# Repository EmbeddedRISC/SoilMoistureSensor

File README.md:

# SoilMoistureSensor
Contains data for Arduino Based Soil Moisture Sensors

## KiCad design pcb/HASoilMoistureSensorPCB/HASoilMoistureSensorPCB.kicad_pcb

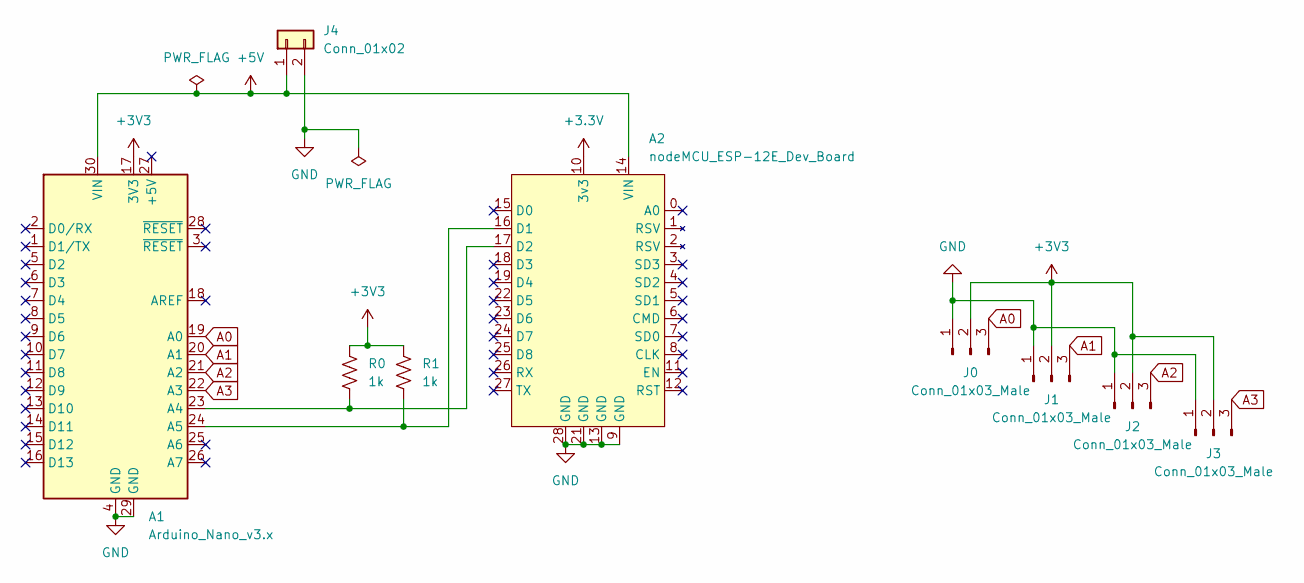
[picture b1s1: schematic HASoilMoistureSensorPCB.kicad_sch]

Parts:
A1: Arduino_Nano_v3.x; Arduino_Nano
A2: nodeMCU_ESP-12E_Dev_Board; nodeMCU_ESP-12e_Through-Hole
J0, J1, J2, J3: Conn_01x03_Male; JST_PH_B3B-PH-K_1x03_P2.00mm_Vertical
J4: Conn_01x02; JST_PH_B2B-PH-K_1x02_P2.00mm_Vertical
R0, R1: 1k; R_Axial_DIN0207_L6.3mm_D2.5mm_P2.54mm_Vertical

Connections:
+3.3V: A2.10 (3v3), A2.20 (3v3), A2.29 (3v3)
+3V3: A1.17 (3V3), J0.2, J1.2, J2.2, J3.2, R0.1, R1.1
+5V: A1.30 (VIN), A2.14 (VIN), J4.1
A0: A1.19 (A0), J0.3
A1: A1.20 (A1), J1.3
A2: A1.21 (A2), J2.3
A3: A1.22 (A3), J3.3
GND: A1.4 (GND), A1.29 (GND), A2.9 (GND), A2.13 (GND), A2.21 (GND), A2.28 (GND), J0.1, J1.1, J2.1, J3.1, J4.2
unnamed: A1.23 (A4), A2.17 (D2), R0.2
unnamed: A1.24 (A5), A2.16 (D1), R1.2

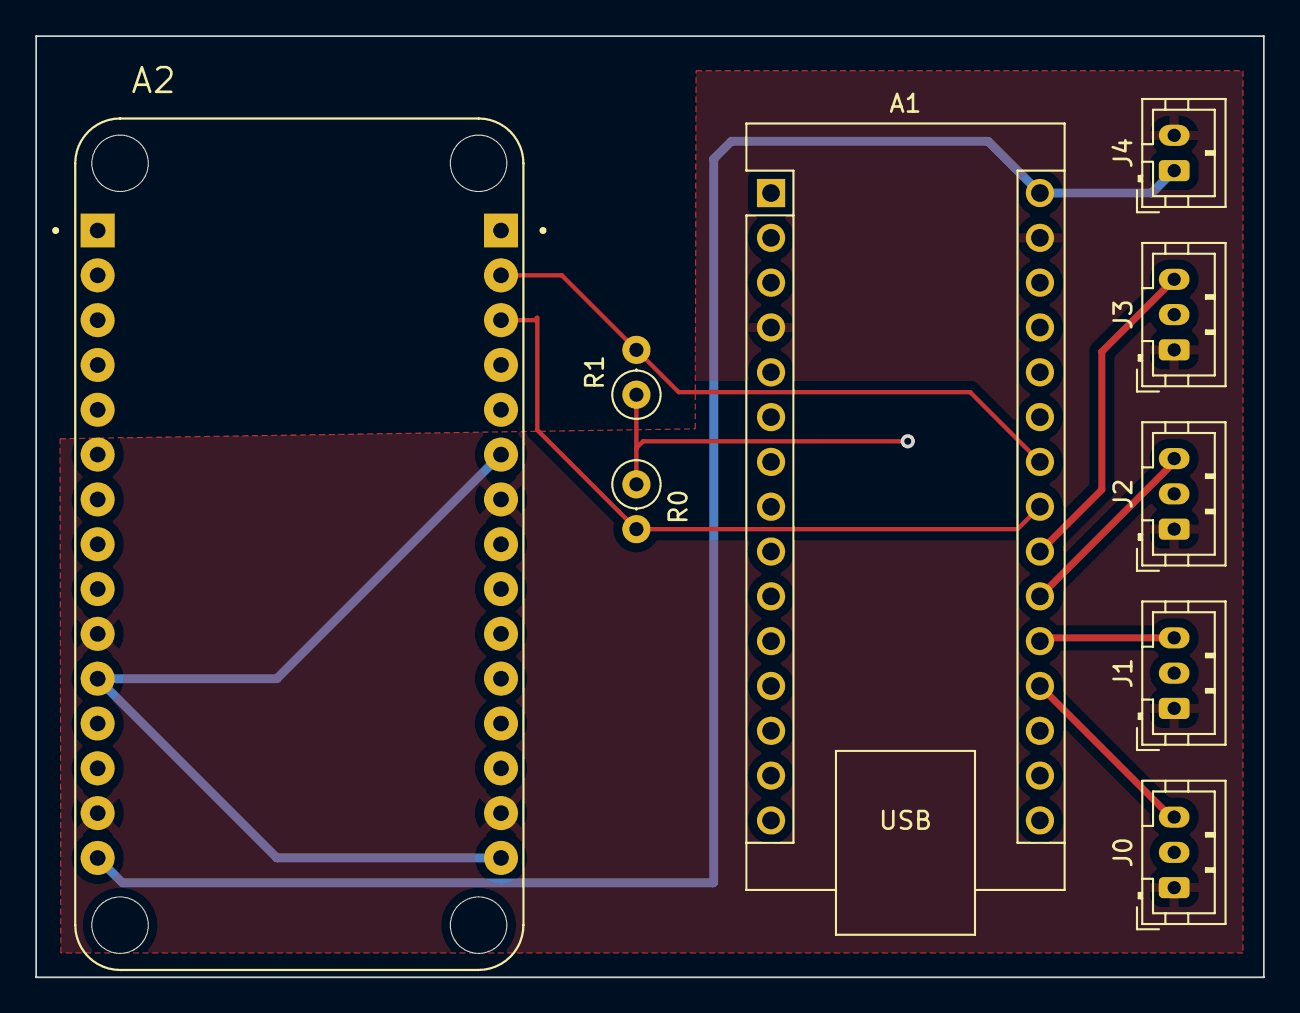
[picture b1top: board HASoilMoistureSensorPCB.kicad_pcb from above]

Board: 2 copper layers, 69.6 x 53.3 mm, 9 parts (0 on the bottom side), 10 nets.

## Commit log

2022-11-22 Working W/ Home-Assistant MQTT
2022-11-23 Working initial build, w/ schematic and initial PCB design
2022-12-16 Fixed default name

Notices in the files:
pcb/HASoilMoistureSensorPCB/HASoilMoistureSensorPCB.kicad_pcb:
Copyright (C) 2022 - Benjamin Davis
Distributed under GNU Piblic License v3
pcb/HASoilMoistureSensorPCB/HASoilMoistureSensorPCB.kicad_sch:
Distributed under GNU General Public License v3
